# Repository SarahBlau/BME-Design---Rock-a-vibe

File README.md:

# BME-Design---Rock-a-vibe
Two semester design course

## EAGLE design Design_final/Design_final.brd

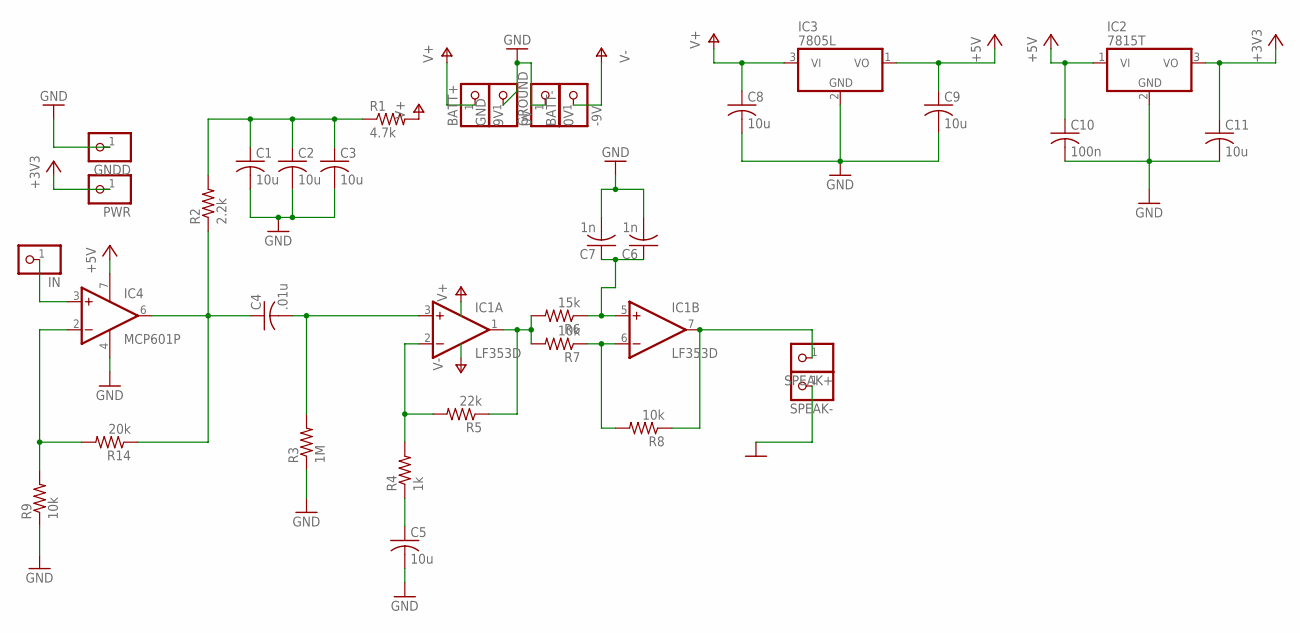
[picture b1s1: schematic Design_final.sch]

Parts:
BATT+: 9V; 1X01
BATT-: -9V; 1X01
C1, C2, C3, C5, C8, C9, C11: 10u; C0805
C4: .01u; C0805
C6, C7: 1n; C0805
C10: 100n; C0805
GND: 0V; 1X01
GNDD: PINHD-1X1; 1X01
GROUND: 0V; 1X01
IC1: LF353D; SO08
IC2: 7815T; TO220H
IC3: 7805L; TO92
IC4: MCP601P; DIL08
IN: PINHD-1X1; 1X01
PWR: PINHD-1X1; 1X01
R1: 4.7k; M0805
R2: 2.2k; M0805
R3: 1M; M0805
R4: 1k; M0805
R5: 22k; M0805
R6: 15k; M0805
R7, R8, R9: 10k; M0805
R14: 20k; M0805
SPEAK+: PINHD-1X1; 1X01
SPEAK-: PINHD-1X1; 1X01

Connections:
+3V3: C11.1, IC2.3 (VO), PWR.1
+5V: C9.1, C10.1, IC2.1 (VI), IC3.1 (VO), IC4.7 (V+)
GND: C1.2, C2.2, C3.2, C5.2, C6.2, C7.2, C8.2, C9.2, C10.2, C11.2, GND.1, GNDD.1, GROUND.1, IC2.2 (GND), IC3.2 (GND), IC4.4 (V-), R3.1, R9.1, SPEAK-.1
unnamed: C1.1, C2.1, C3.1, R1.1, R2.2
unnamed: IC1.6 (-IN), R7.1, R8.2
unnamed: IC4.3 (+IN), IN.1
unnamed: C4.1, IC4.6 (OUT), R2.1, R14.1
unnamed: C4.2, IC1.3 (+IN), R3.2
unnamed: IC1.2 (-IN), R4.2, R5.2
unnamed: C5.1, R4.1
unnamed: IC1.1 (OUT), R5.1, R6.2, R7.2
unnamed: IC1.7 (OUT), R8.1, SPEAK+.1
unnamed: C6.1, C7.1, IC1.5 (+IN), R6.1
unnamed: IC4.2 (-IN), R9.2, R14.2
V+: BATT+.1, C8.1, IC1.8 (V+), IC3.3 (VI), R1.2
V-: BATT-.1, IC1.4 (V-)

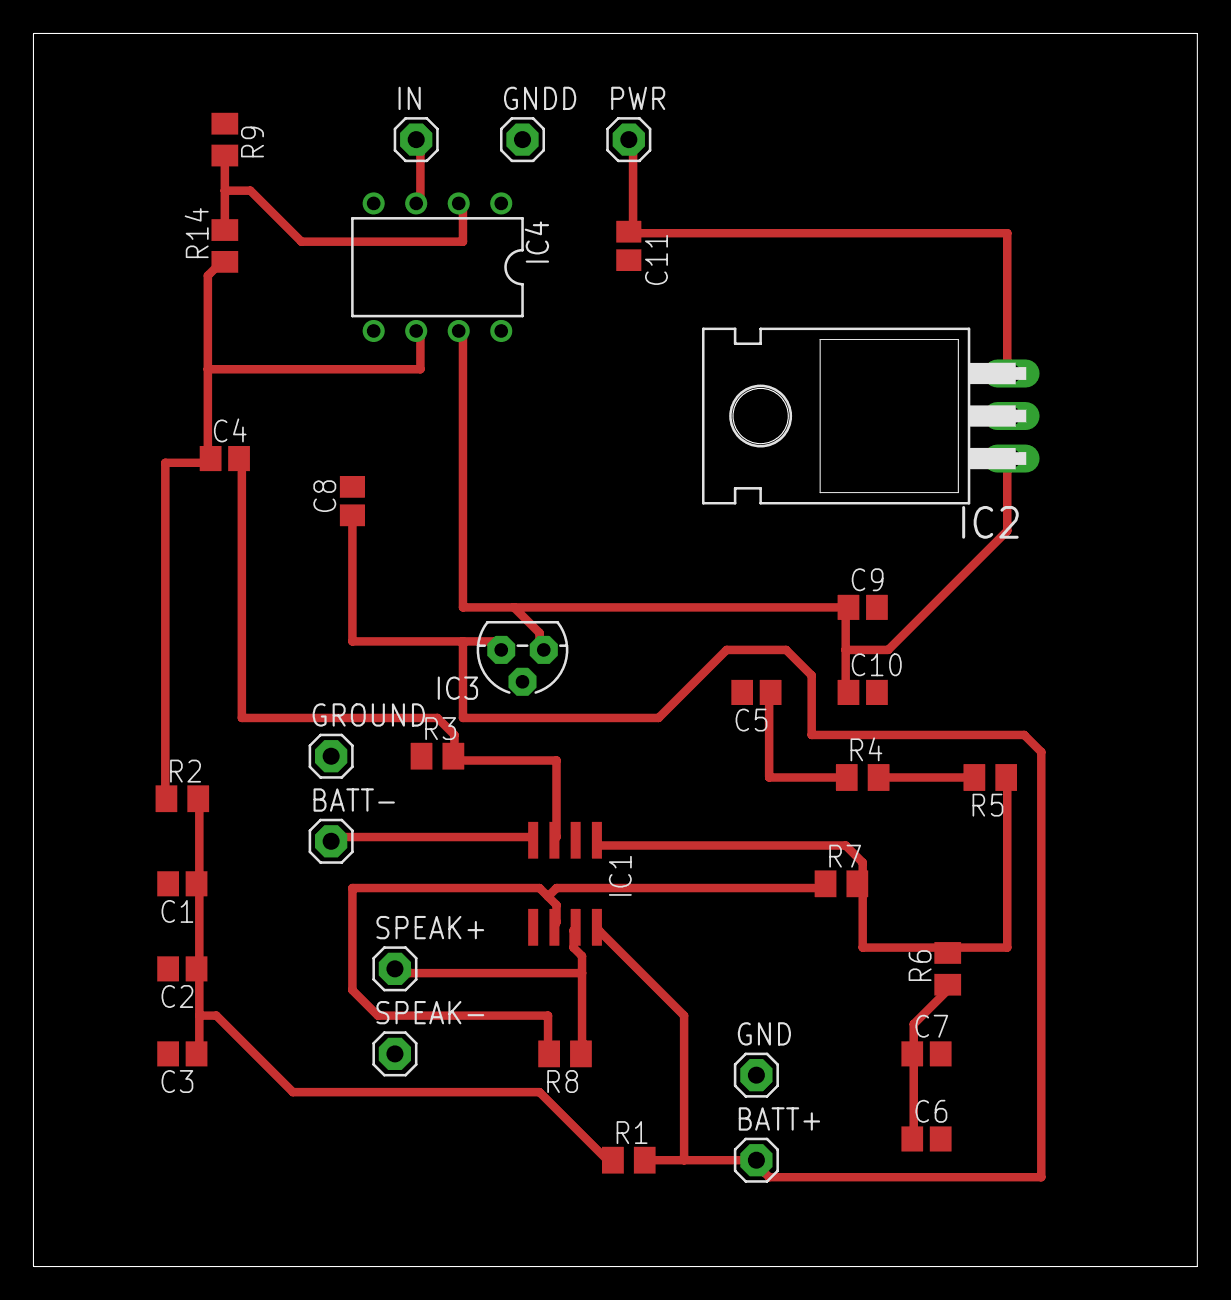
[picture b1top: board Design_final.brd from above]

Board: 2 copper layers, 69.5 x 73.7 mm, 34 parts (0 on the bottom side), 16 nets.

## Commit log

2018-12-04 Create Research
2018-12-04 Create Research info
2018-12-04 Add files via upload
    Design guide from Sorbothane website
2018-12-06 Add files via upload
    Sorbothane product guide
2019-04-19 Final PCB design
2019-04-19 New final
